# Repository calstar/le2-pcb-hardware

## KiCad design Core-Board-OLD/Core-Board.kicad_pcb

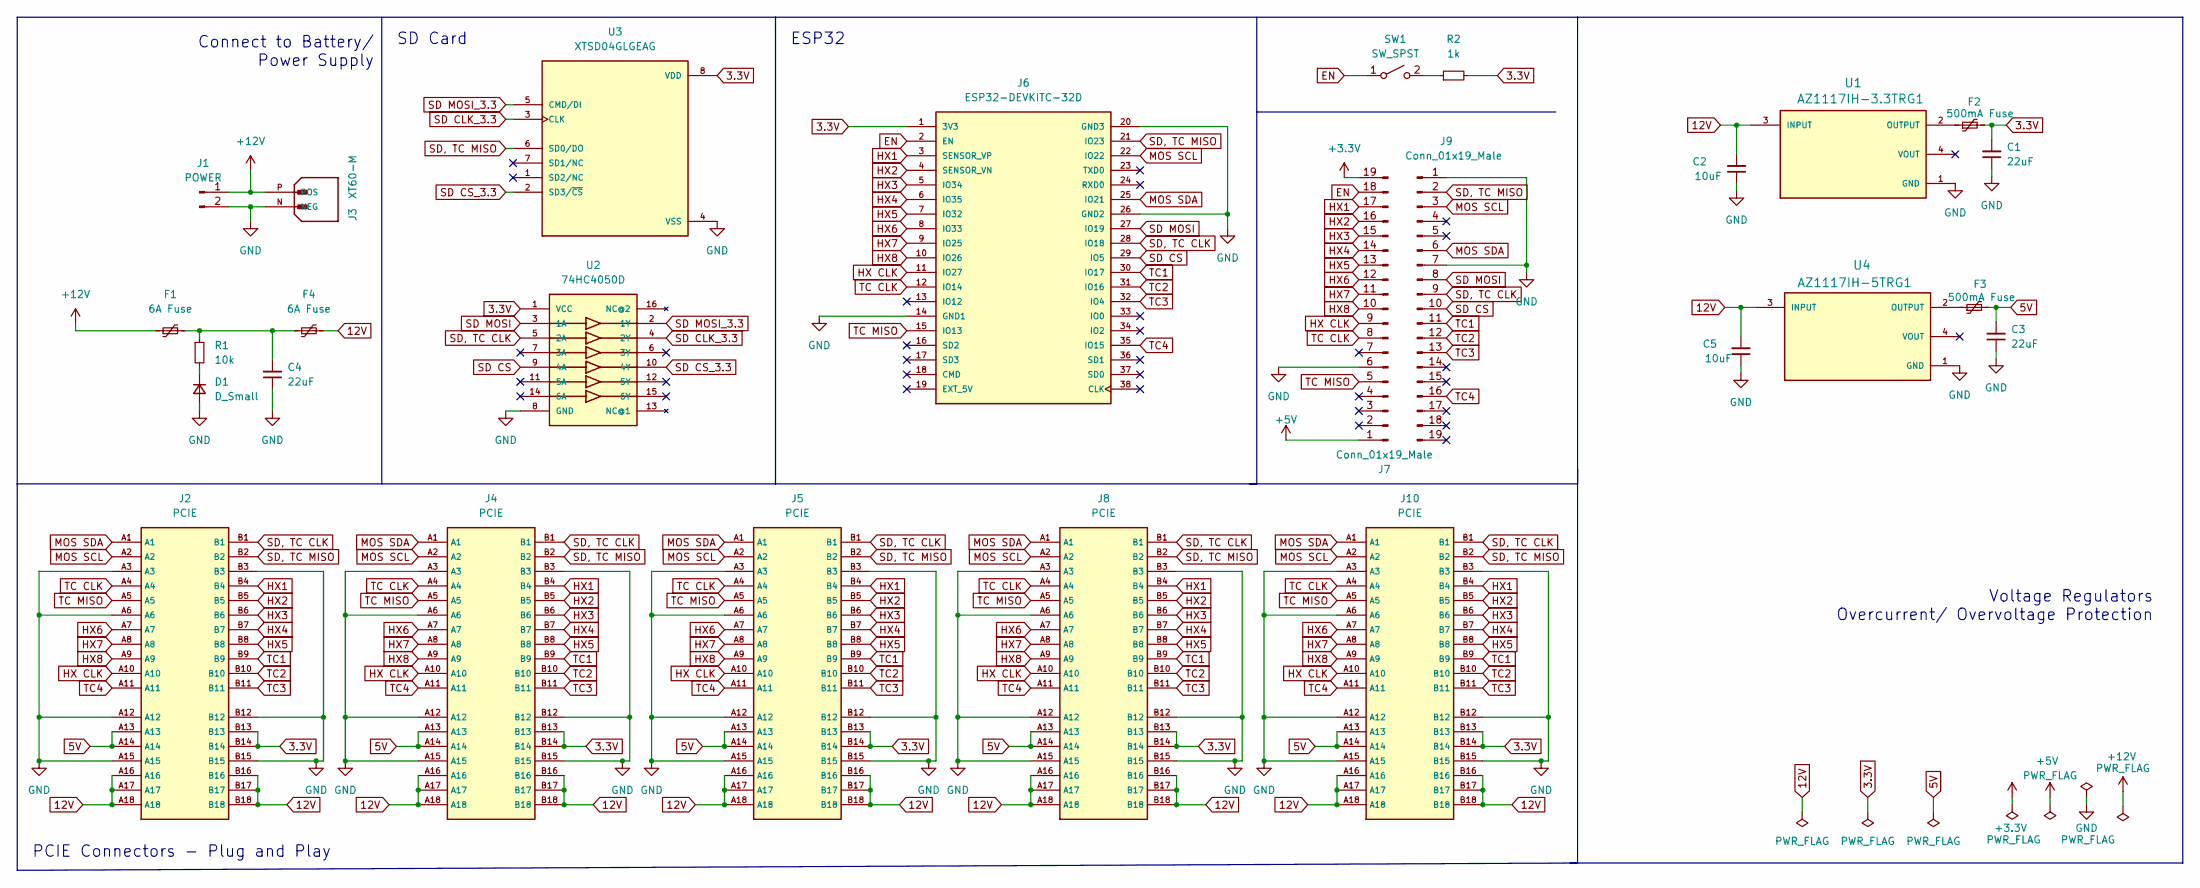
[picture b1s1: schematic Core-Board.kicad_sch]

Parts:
C1, C3, C4: 22uF; C_0603_1608Metric
C2, C5: 10uF; C_0603_1608Metric
D1: D_Small; D_0603_1608Metric
F1, F4: 6A Fuse; Fuse_2920_7451Metric
F2, F3: 500mA Fuse; Fuse_0603_1608Metric
J1: POWER; Banana_Jack_2Pin
J2, J4, J5, J8, J10: PCIE; AMPHENOL_10018784-10210TLF; PARTREV B
J3: XT60-M; AMASS_XT60-M; PARTREV V1.2
J6: ESP32-DEVKITC-32D; MODULE_ESP32-DEVKITC-32D; PARTREV 4
J7, J9: Conn_01x19_Male; PinHeader_1x19_P2.54mm_Vertical
R1: 10k; R_0603_1608Metric
R2: 1k; R_0603_1608Metric
SW1: SW_SPST; SW_PUSH_6mm
U1: AZ1117IH-3.3TRG1; SOT230P700X185-4N; PARTREV 2-2
U2: 74HC4050D; SO16
U3: XTSD04GLGEAG; SON127P600X800X95-8N; PARTREV 3.1
U4: AZ1117IH-5TRG1; SOT230P700X185-4N; PARTREV 2-2

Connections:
3.3V: C1.2, F2.2, J2.B13, J2.B14, J4.B13, J4.B14, J5.B13, J5.B14, J6.1 (3V3), J8.B13, J8.B14, J10.B13, J10.B14, R2.2, U2.1 (VCC), U3.8 (VDD)
5V: C3.2, F3.2, J2.A13, J2.A14, J4.A13, J4.A14, J5.A13, J5.A14, J8.A13, J8.A14, J10.A13, J10.A14
12V: C2.2, C5.2, F4.2, J2.A16, J2.A17, J2.A18, J2.B16, J2.B17, J2.B18, J4.A16, J4.A17, J4.A18, J4.B16, J4.B17, J4.B18, J5.A16, J5.A17, J5.A18, J5.B16, J5.B17, J5.B18, J8.A16, J8.A17, J8.A18, J8.B16, J8.B17, J8.B18, J10.A16, J10.A17, J10.A18, J10.B16, J10.B17, J10.B18, U1.3 (INPUT), U4.3 (INPUT)
+3.3V: J7.19
+5V: J7.1
+12V: F1.1, J1.1, J3.P (POS)
EN: J6.2 (EN), J7.18, SW1.1 (A)
GND: C1.1, C2.1, C3.1, C4.1, C5.1, D1.2 (A), J1.2, J2.A3, J2.A6, J2.A12, J2.A15, J2.B3, J2.B12, J2.B15, J3.N (NEG), J4.A3, J4.A6, J4.A12, J4.A15, J4.B3, J4.B12, J4.B15, J5.A3, J5.A6, J5.A12, J5.A15, J5.B3, J5.B12, J5.B15, J6.14 (GND1), J6.20 (GND3), J6.26 (GND2), J7.6, J8.A3, J8.A6, J8.A12, J8.A15, J8.B3, J8.B12, J8.B15, J9.1, J9.7, J10.A3, J10.A6, J10.A12, J10.A15, J10.B3, J10.B12, J10.B15, U1.1 (GND), U2.8 (GND), U3.4 (VSS), U4.1 (GND)
HX1: J2.B4, J4.B4, J5.B4, J6.3 (SENSOR_VP), J7.17, J8.B4, J10.B4
HX2: J2.B5, J4.B5, J5.B5, J6.4 (SENSOR_VN), J7.16, J8.B5, J10.B5
HX3: J2.B6, J4.B6, J5.B6, J6.5 (IO34), J7.15, J8.B6, J10.B6
HX4: J2.B7, J4.B7, J5.B7, J6.6 (IO35), J7.14, J8.B7, J10.B7
HX5: J2.B8, J4.B8, J5.B8, J6.7 (IO32), J7.13, J8.B8, J10.B8
HX6: J2.A7, J4.A7, J5.A7, J6.8 (IO33), J7.12, J8.A7, J10.A7
HX7: J2.A8, J4.A8, J5.A8, J6.9 (IO25), J7.11, J8.A8, J10.A8
HX8: J2.A9, J4.A9, J5.A9, J6.10 (IO26), J7.10, J8.A9, J10.A9
HX CLK: J2.A10, J4.A10, J5.A10, J6.11 (IO27), J7.9, J8.A10, J10.A10
MOS SCL: J2.A2, J4.A2, J5.A2, J6.22 (IO22), J8.A2, J9.3, J10.A2
MOS SDA: J2.A1, J4.A1, J5.A1, J6.25 (IO21), J8.A1, J9.6, J10.A1
unnamed: C4.2, F1.2, F4.1, R1.1
unnamed: D1.1 (K), R1.2
unnamed: F2.1, U1.2 (OUTPUT)
unnamed: F3.1, U4.2 (OUTPUT)
unnamed: R2.1, SW1.2 (B)
SD CLK_3.3: U2.4 (2Y), U3.3 (CLK)
SD CS: J6.29 (IO5), J9.10, U2.9 (4A)
SD CS_3.3: U2.10 (4Y), U3.2 (SD3/~CS)
SD MOSI: J6.27 (IO19), J9.8, U2.3 (1A)
SD MOSI_3.3: U2.2 (1Y), U3.5 (CMD/DI)
SD, TC CLK: J2.B1, J4.B1, J5.B1, J6.28 (IO18), J8.B1, J9.9, J10.B1, U2.5 (2A)
SD, TC MISO: J2.B2, J4.B2, J5.B2, J6.21 (IO23), J8.B2, J9.2, J10.B2, U3.6 (SD0/DO)
TC1: J2.B9, J4.B9, J5.B9, J6.30 (IO17), J8.B9, J9.11, J10.B9
TC2: J2.B10, J4.B10, J5.B10, J6.31 (IO16), J8.B10, J9.12, J10.B10
TC3: J2.B11, J4.B11, J5.B11, J6.32 (IO4), J8.B11, J9.13, J10.B11
TC4: J2.A11, J4.A11, J5.A11, J6.35 (IO15), J8.A11, J9.16, J10.A11
TC CLK: J2.A4, J4.A4, J5.A4, J6.12 (IO14), J7.8, J8.A4, J10.A4
TC MISO: J2.A5, J4.A5, J5.A5, J6.15 (IO13), J7.5, J8.A5, J10.A5

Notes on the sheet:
PCIE Connectors - Plug and Play
SD Card
ESP32
Voltage Regulators Overcurrent/ Overvoltage Protection
Connect to Battery/ Power Supply

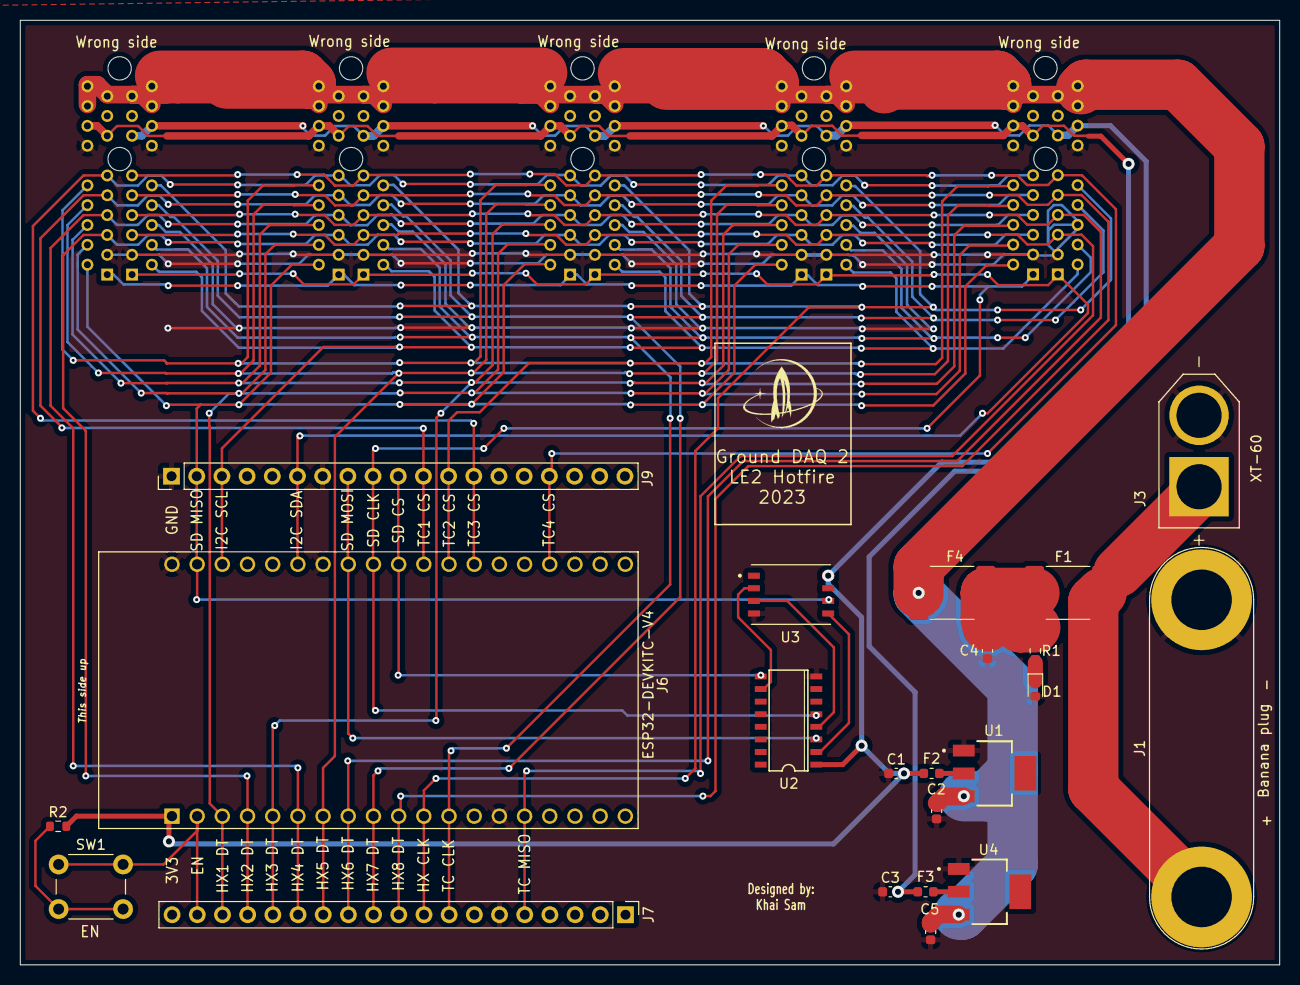
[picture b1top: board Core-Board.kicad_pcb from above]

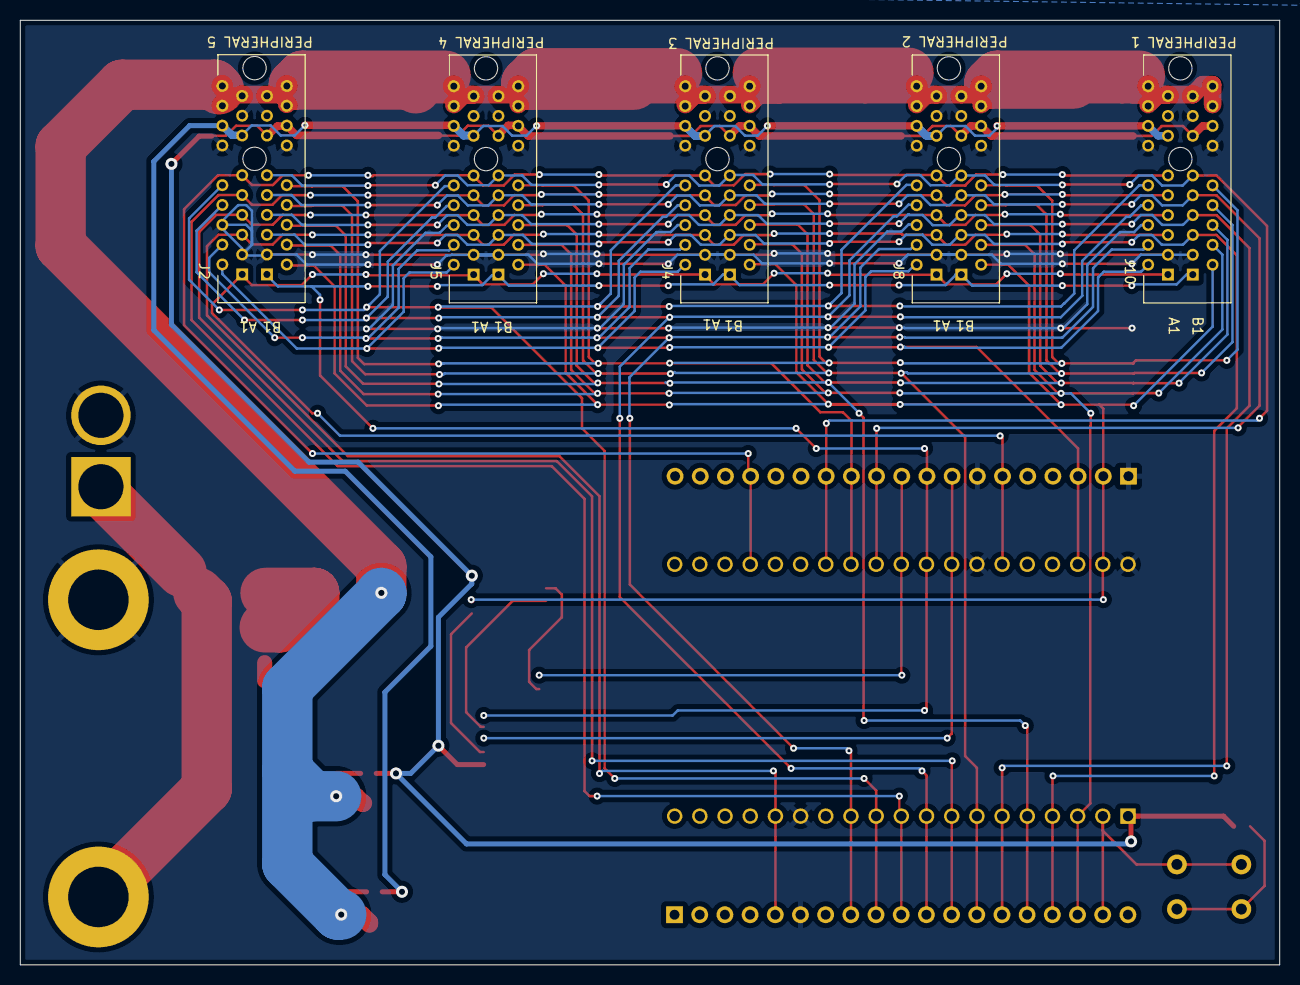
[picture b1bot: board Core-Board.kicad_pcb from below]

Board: 2 copper layers, 127.0 x 95.2 mm, 27 parts (5 on the bottom side), 35 nets.

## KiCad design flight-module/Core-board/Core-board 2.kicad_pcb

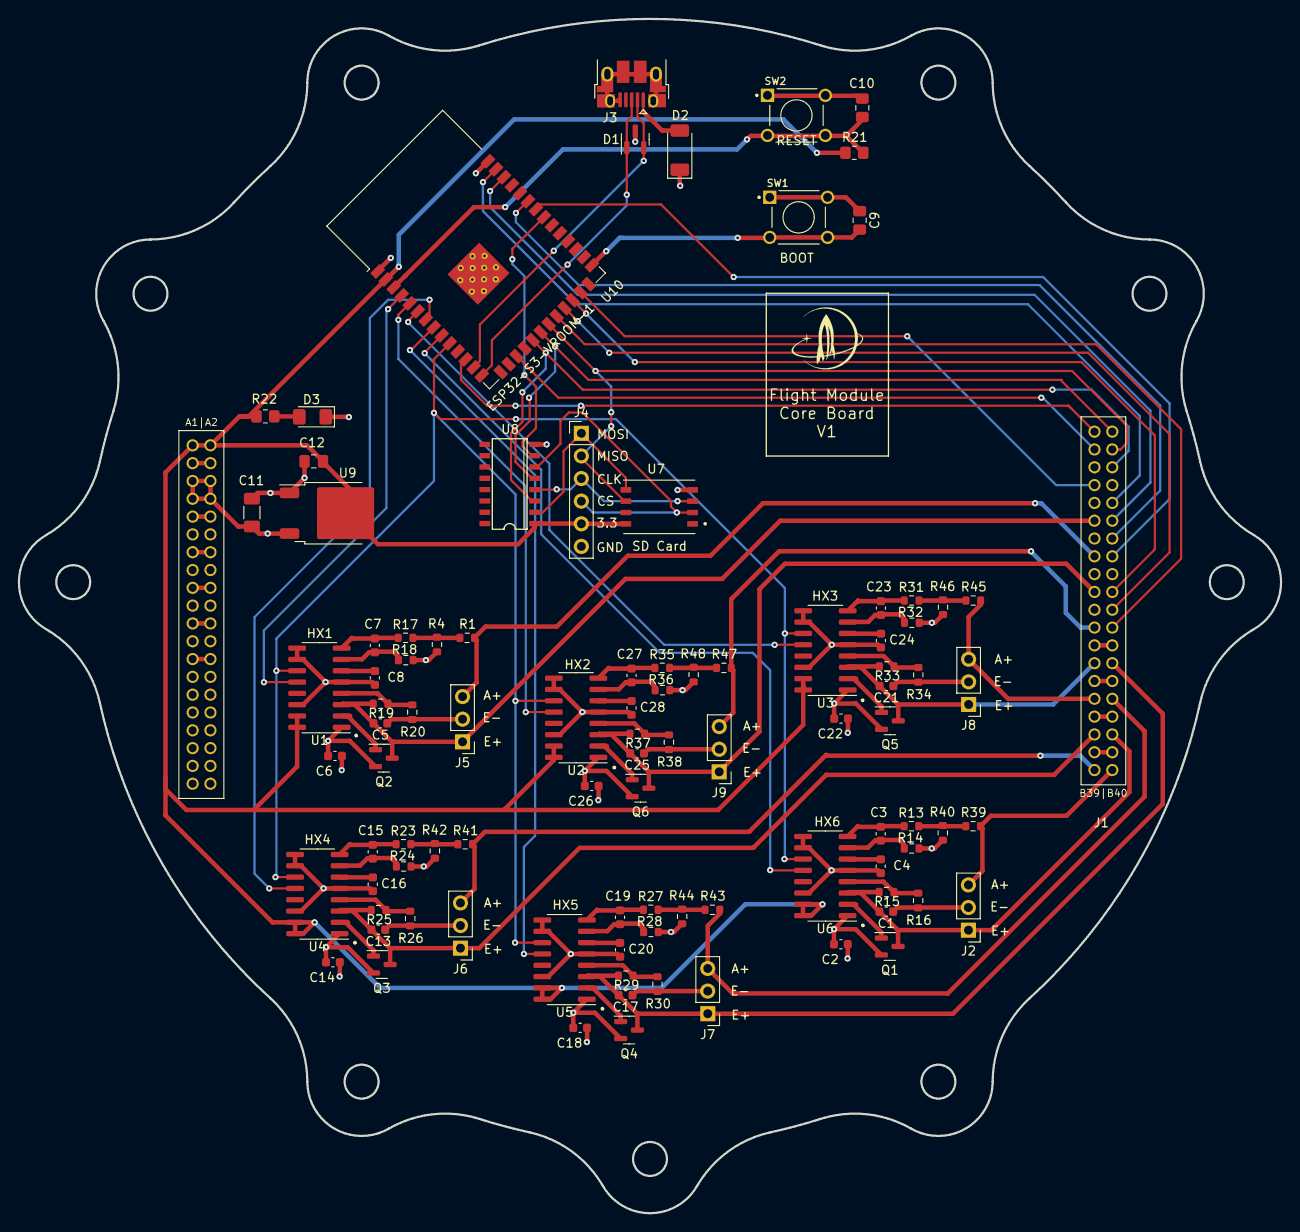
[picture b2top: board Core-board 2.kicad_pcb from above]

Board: 4 copper layers, 141.7 x 134.1 mm, 96 parts (0 on the bottom side), 81 nets.

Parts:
C1, C2, C5, C6, C13, C14, C17, C18, C21, C22, C25, C26: 10uF; C_0603_1608Metric
C3, C4, C7, C8, C15, C16, C19, C20, C23, C24, C27, C28: 0.1uF; C_0603_1608Metric
C9, C10: 1uF; C_0805_2012Metric_Pad1.18x1.45mm_HandSolder
C11: 10uF; C_1206_3216Metric_Pad1.33x1.80mm_HandSolder
C12: 22uF; C_0805_2012Metric_Pad1.18x1.45mm_HandSolder
D1: PESD12VL2BT; SOT-23
D2: D_Schottky; D_SOD-128
D3: GREEN; LED_1206_3216Metric_Pad1.42x1.75mm_HandSolder
J1: Stack_Shape
J2, J5, J6, J7, J8, J9: Conn_01x03_Pin; PinHeader_1x03_P2.54mm_Vertical
J3: USB_B_Micro; USB_Micro-B_Amphenol_10103594-0001LF_Horizontal
J4: Conn_01x06_Pin; PinHeader_1x06_P2.54mm_Vertical
Q1, Q2, Q3, Q4, Q5, Q6: MMBT4403LT3G; SOT-23
R1, R39, R41, R43, R45, R47: 100kΩ; R_0603_1608Metric
R4, R40, R42, R44, R46, R48: 2kΩ; R_0603_1608Metric
R13, R14, R17, R18, R23, R24, R27, R28, R31, R32, R35, R36: 100Ω; R_0603_1608Metric
R15, R19, R25, R29, R33, R37: 20kΩ; R_0603_1608Metric
R16, R20, R26, R30, R34, R38: 8.2kΩ; R_0603_1608Metric
R21: 10k; R_0805_2012Metric_Pad1.20x1.40mm_HandSolder
R22: 300; R_0805_2012Metric_Pad1.20x1.40mm_HandSolder
SW1, SW2: 1825910-6; SW_1825910-6-4
U1, U2, U3, U4, U5, U6: HX711; SOP-16_3.9x9.9mm_P1.27mm
U7: XTSD04GLGEAG; SON127P600X800X95-8N
U8: 74HC4050D; SO16
U9: AZ1084-3.3; TO-252-2
U10: ESP32-S3-WROOM-1-N16R2; ESP32-S3-WROOM-1

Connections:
+3.3V: C12.1, J1.A1 (Pin_1), J1.A2 (Pin_2), J4.5, R21.1, R22.2, U1.15 (RATE), U1.16 (DVDD), U2.15 (RATE), U2.16 (DVDD), U3.15 (RATE), U3.16 (DVDD), U4.15 (RATE), U4.16 (DVDD), U5.15 (RATE), U5.16 (DVDD), U6.15 (RATE), U6.16 (DVDD), U7.8 (VDD), U8.1 (VCC), U9.2 (VO), U10.2 (3V3)
+5V: C2.2, C6.2, C11.1, C14.2, C18.2, C22.2, C26.2, D2.1 (K), J1.A5 (Pin_5), J1.A6 (Pin_6), J1.A7 (Pin_7), J1.A8 (Pin_8), Q1.2 (E), Q2.2 (E), Q3.2 (E), Q4.2 (E), Q5.2 (E), Q6.2 (E), U1.1 (VSUP), U2.1 (VSUP), U3.1 (VSUP), U4.1 (VSUP), U5.1 (VSUP), U6.1 (VSUP), U9.3 (VI)
/ESP32-S3-WROOM-1-Breakout/BOOT: C9.1, SW1.3, SW1.4, U10.27 (IO0)
/ESP32-S3-WROOM-1-Breakout/EN: C10.1, R21.2, SW2.3, SW2.4, U10.3 (EN)
/ESP32-S3-WROOM-1-Breakout/USB_D+: D1.1 (K), J3.3 (D+), U10.14 (IO20)
/ESP32-S3-WROOM-1-Breakout/USB_D-: D1.2 (K), J3.2 (D-), U10.13 (IO19)
/HX1_A+: J1.B15 (Pin_15), J5.3, R1.1
/HX1_DT: U1.12 (DOUT), U10.4 (IO4)
/HX1_E+: C5.2, J1.B11 (Pin_11), J5.1, Q2.3 (C), R19.2, U1.3 (AVDD)
/HX2_A+: J1.B23 (Pin_23), J9.3, R47.1
/HX2_DT: U2.12 (DOUT), U10.5 (IO5)
/HX2_E+: C25.2, J1.B19 (Pin_19), J9.1, Q6.3 (C), R37.2, U2.3 (AVDD)
/HX3_A+: J1.B31 (Pin_31), J8.3, R45.1
/HX3_DT: U3.12 (DOUT), U10.6 (IO6)
/HX3_E+: C21.2, J1.B27 (Pin_27), J8.1, Q5.3 (C), R33.2, U3.3 (AVDD)
/HX4_A+: J1.B39 (Pin_39), J6.3, R41.1
/HX4_DT: U4.12 (DOUT), U10.7 (IO7)
/HX4_E+: C13.2, J1.B35 (Pin_35), J6.1, Q3.3 (C), R25.2, U4.3 (AVDD)
/HX5_A+: J1.B32 (Pin_32), J7.3, R43.1
/HX5_DT: U5.12 (DOUT), U10.8 (IO15)
/HX5_E+: C17.2, J1.B28 (Pin_28), J7.1, Q4.3 (C), R29.2, U5.3 (AVDD)
/HX6_A+: J1.B40 (Pin_40), J2.3, R39.1
/HX6_DT: U6.12 (DOUT), U10.9 (IO16)
/HX6_E+: C1.2, J1.B36 (Pin_36), J2.1, Q1.3 (C), R15.2, U6.3 (AVDD)
/HX_CLK: U1.11 (PD_SCK), U2.11 (PD_SCK), U3.11 (PD_SCK), U4.11 (PD_SCK), U5.11 (PD_SCK), U6.11 (PD_SCK), U10.10 (IO17)
/I2C_SCL: J1.B3 (Pin_3), U10.17 (IO9)
/I2C_SDA: J1.B1 (Pin_1), U10.12 (IO8)
/PYRO1EN: J1.B7 (Pin_7), U10.25 (IO48)
/PYRO2EN: J1.B20 (Pin_20), U10.24 (IO47)
/PYRO3EN: J1.B22 (Pin_22), U10.23 (IO21)
/PYRO4EN: J1.B24 (Pin_24), U10.22 (IO14)
/SD_CS: U8.7 (3A), U10.33 (IO40)
/SD_CS_BUF: J4.4, U7.2 (SD3/~CS), U8.6 (3Y)
/SPI_CLK: J1.B2 (Pin_2), U8.5 (2A), U10.20 (IO12)
/SPI_CLK_BUF: J4.3, U7.3 (CLK), U8.4 (2Y)
/SPI_MISO: J1.B4 (Pin_4), J4.2, U7.6 (SD0/DO), U10.21 (IO13)
/SPI_MOSI: J1.B6 (Pin_6), U8.3 (1A), U10.19 (IO11)
/SPI_MOSI_BUF: J4.1, U7.5 (CMD/DI), U8.2 (1Y)
/TC1_CS: J1.B10 (Pin_10), U10.39 (IO1)
/TC2_CS: J1.B12 (Pin_12), U10.38 (IO2)
/TC3_CS: J1.B14 (Pin_14), U10.35 (IO42)
/TC4_CS: J1.B16 (Pin_16), U10.34 (IO41)
GND: C1.1, C2.1, C4.1, C5.1, C6.1, C8.1, C9.2, C10.2, C11.2, C12.2, C13.1, C14.1, C16.1, C17.1, C18.1, C20.1, C21.1, C22.1, C24.1, C25.1, C26.1, C28.1, D1.3 (A), D3.1 (K), J1.A3 (Pin_3), J1.A4 (Pin_4), J1.A9 (Pin_9), J1.A10 (Pin_10), J1.A13 (Pin_13), J1.A14 (Pin_14), J1.A17 (Pin_17), J1.A18 (Pin_18), J1.A21 (Pin_21), J1.A22 (Pin_22), J1.A25 (Pin_25), J1.A26 (Pin_26), J1.B5 (Pin_5), J1.B8 (Pin_8), J1.B9 (Pin_9), J1.B13 (Pin_13), J1.B17 (Pin_17), J1.B18 (Pin_18), J1.B21 (Pin_21), J1.B25 (Pin_25), J1.B26 (Pin_26), J1.B29 (Pin_29), J1.B30 (Pin_30), J1.B33 (Pin_33), J1.B34 (Pin_34), J1.B37 (Pin_37), J1.B38 (Pin_38), J2.2, J3.5 (GND), J3.6 (Shield), J4.6, J5.2, J6.2, J7.2, J8.2, J9.2, R4.1, R14.2, R16.1, R18.2, R20.1, R24.2, R26.1, R28.2, R30.1, R32.2, R34.1, R36.2, R38.1, R40.1, R42.1, R44.1, R46.1, R48.1, SW1.1, SW1.2, SW2.1, SW2.2, U1.5 (AGND), U1.9 (INB-), U1.10 (INB+), U1.14 (XI), U2.5 (AGND), U2.9 (INB-), U2.10 (INB+), U2.14 (XI), U3.5 (AGND), U3.9 (INB-), U3.10 (INB+), U3.14 (XI), U4.5 (AGND), U4.9 (INB-), U4.10 (INB+), U4.14 (XI), U5.5 (AGND), U5.9 (INB-), U5.10 (INB+), U5.14 (XI), U6.5 (AGND), U6.9 (INB-), U6.10 (INB+), U6.14 (XI), U7.4 (VSS), U8.8 (GND), U9.1 (GND), U10.1 (GND), U10.40 (GND__1), U10.41 (GND__2)
unnamed: D2.2 (A), J3.1 (VBUS)
unnamed: D3.2 (A), R22.1
unnamed: Q1.1 (B), U6.2 (BASE)
unnamed: Q2.1 (B), U1.2 (BASE)
unnamed: Q3.1 (B), U4.2 (BASE)
unnamed: Q4.1 (B), U5.2 (BASE)
unnamed: Q5.1 (B), U3.2 (BASE)
unnamed: Q6.1 (B), U2.2 (BASE)
unnamed: R1.2, R4.2, R17.2
unnamed: R13.2, R39.2, R40.2
unnamed: R23.2, R41.2, R42.2
unnamed: R27.2, R43.2, R44.2
unnamed: R31.2, R45.2, R46.2
unnamed: R35.2, R47.2, R48.2
unnamed: C7.2, R17.1, U1.8 (INA+)
unnamed: C7.1, R18.1, U1.7 (INA-)
unnamed: C8.2, U1.6 (VBG)
unnamed: R19.1, R20.2, U1.4 (VFB)
unnamed: C27.2, R35.1, U2.8 (INA+)
unnamed: C27.1, R36.1, U2.7 (INA-)
unnamed: C28.2, U2.6 (VBG)
unnamed: R37.1, R38.2, U2.4 (VFB)
unnamed: C23.2, R31.1, U3.8 (INA+)
unnamed: C23.1, R32.1, U3.7 (INA-)
unnamed: C24.2, U3.6 (VBG)
unnamed: R33.1, R34.2, U3.4 (VFB)
unnamed: C15.2, R23.1, U4.8 (INA+)
unnamed: C15.1, R24.1, U4.7 (INA-)
unnamed: C16.2, U4.6 (VBG)
unnamed: R25.1, R26.2, U4.4 (VFB)
unnamed: C19.2, R27.1, U5.8 (INA+)
unnamed: C19.1, R28.1, U5.7 (INA-)
unnamed: C20.2, U5.6 (VBG)
unnamed: R29.1, R30.2, U5.4 (VFB)
unnamed: C3.2, R13.1, U6.8 (INA+)
unnamed: C3.1, R14.1, U6.7 (INA-)
unnamed: C4.2, U6.6 (VBG)
unnamed: R15.1, R16.2, U6.4 (VFB)

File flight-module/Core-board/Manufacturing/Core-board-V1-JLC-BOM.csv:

Comment,Designator,Footprint,LCSC
10uF,"C1,C2,C5,C6,C13,C14,C17,C18,C21,C22,C25,C26",Capacitor_SMD:C_0603_1608Metric,
10uF,C11,Capacitor_SMD:C_1206_3216Metric_Pad1.33x1.80mm_HandSolder,
22uF,C12,Capacitor_SMD:C_0805_2012Metric_Pad1.18x1.45mm_HandSolder,
0.1uF,"C3,C4,C7,C8,C15,C16,C19,C20,C23,C24,C27,C28",Capacitor_SMD:C_0603_1608Metric,
1uF,"C9,C10",Capacitor_SMD:C_0805_2012Metric_Pad1.18x1.45mm_HandSolder,
PESD12VL2BT,D1,Package_TO_SOT_SMD:SOT-23,
"PMEG3050EP,115",D2,Diode_SMD:D_SOD-128,
EL0603/GHC-C01/DT,D3,LED_SMD:LED_1206_3216Metric_Pad1.42x1.75mm_HandSolder,
MMBT4403LT3G,"Q1,Q2,Q3,Q4,Q5,Q6",Package_TO_SOT_SMD:SOT-23,
100Ω,"R13,R14,R17,R18,R23,R24,R27,R28,R31,R32,R35,R36",Resistor_SMD:R_0603_1608Metric,
20kΩ,"R15,R19,R25,R29,R33,R37",Resistor_SMD:R_0603_1608Metric,
8.2kΩ,"R16,R20,R26,R30,R34,R38",Resistor_SMD:R_0603_1608Metric,
10k,R21,Resistor_SMD:R_0805_2012Metric_Pad1.20x1.40mm_HandSolder,
300,R22,Resistor_SMD:R_0805_2012Metric_Pad1.20x1.40mm_HandSolder,
100kΩ,"R1,R39,R41,R43,R45,R47",Resistor_SMD:R_0603_1608Metric,
2kΩ,"R4,R40,R42,R44,R46,R48",Resistor_SMD:R_0603_1608Metric,
1825910-6,"SW1,SW2",Button_Switch_SMD:SW_SPST_TL3305A,
ESP32-S3-WROOM-1-N16R2,U10,RF_Module:ESP32-S3-WROOM-1,
XTSD04GLGEAG,U7,XTSD04GLGEAG:SON127P600X800X95-8N,
74HC4050D,U8,74HC4050D:SO16,
AZ1084-3.3,U9,Package_TO_SOT_SMD:TO-252-2,

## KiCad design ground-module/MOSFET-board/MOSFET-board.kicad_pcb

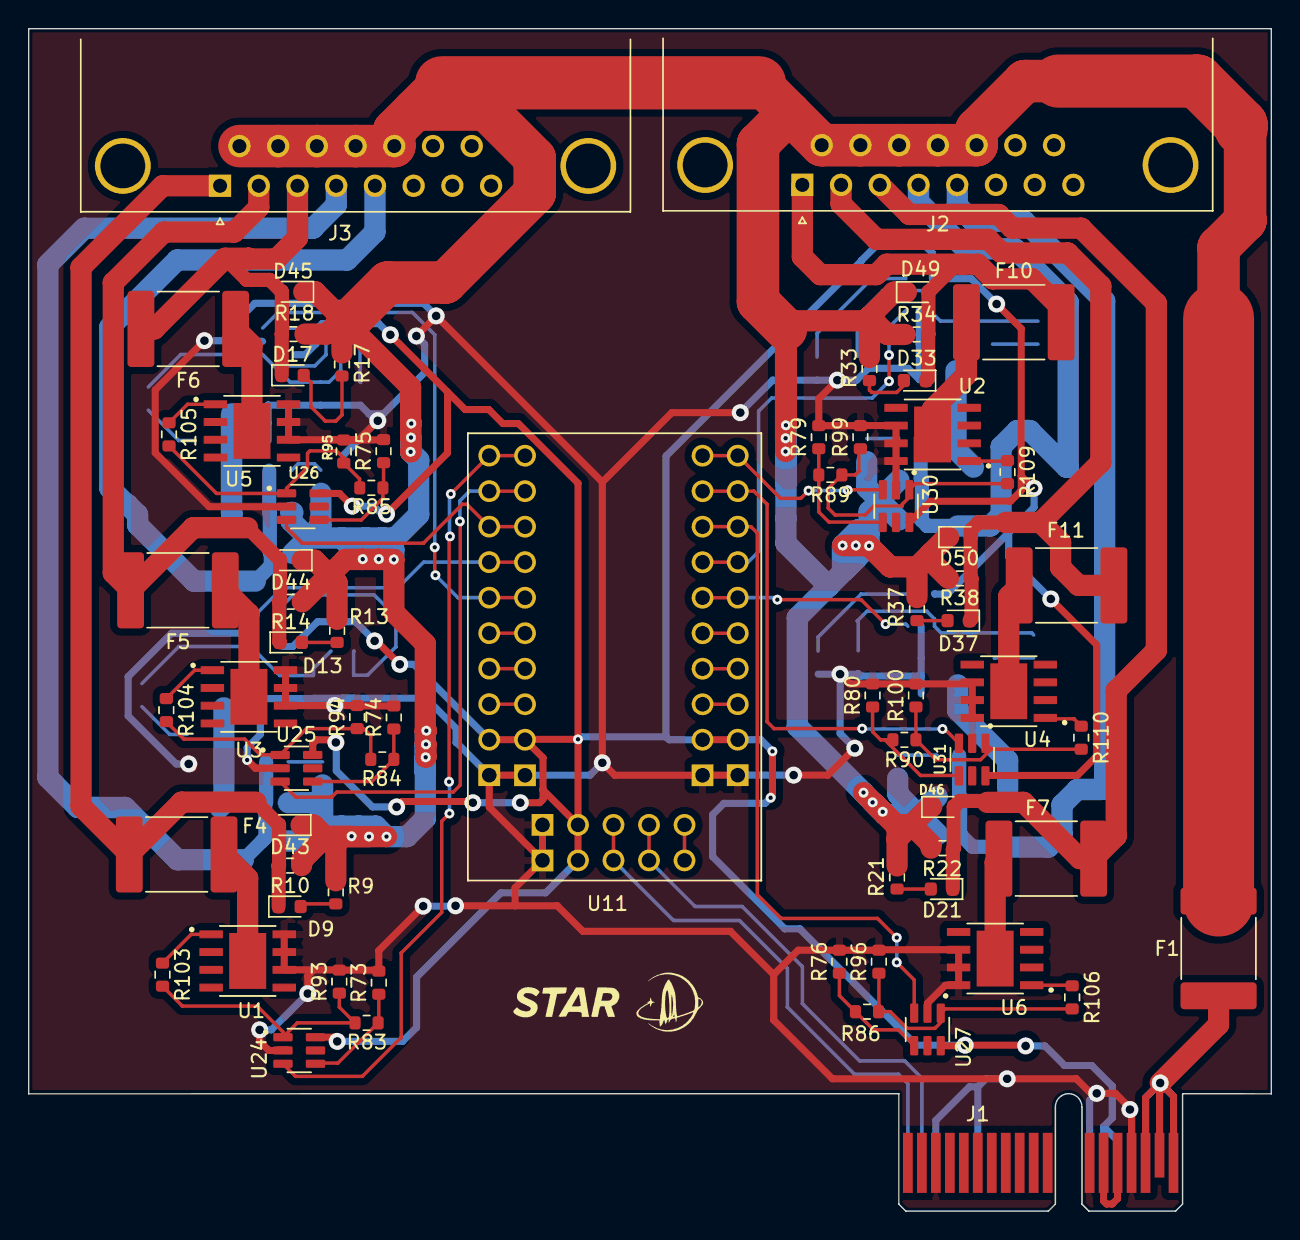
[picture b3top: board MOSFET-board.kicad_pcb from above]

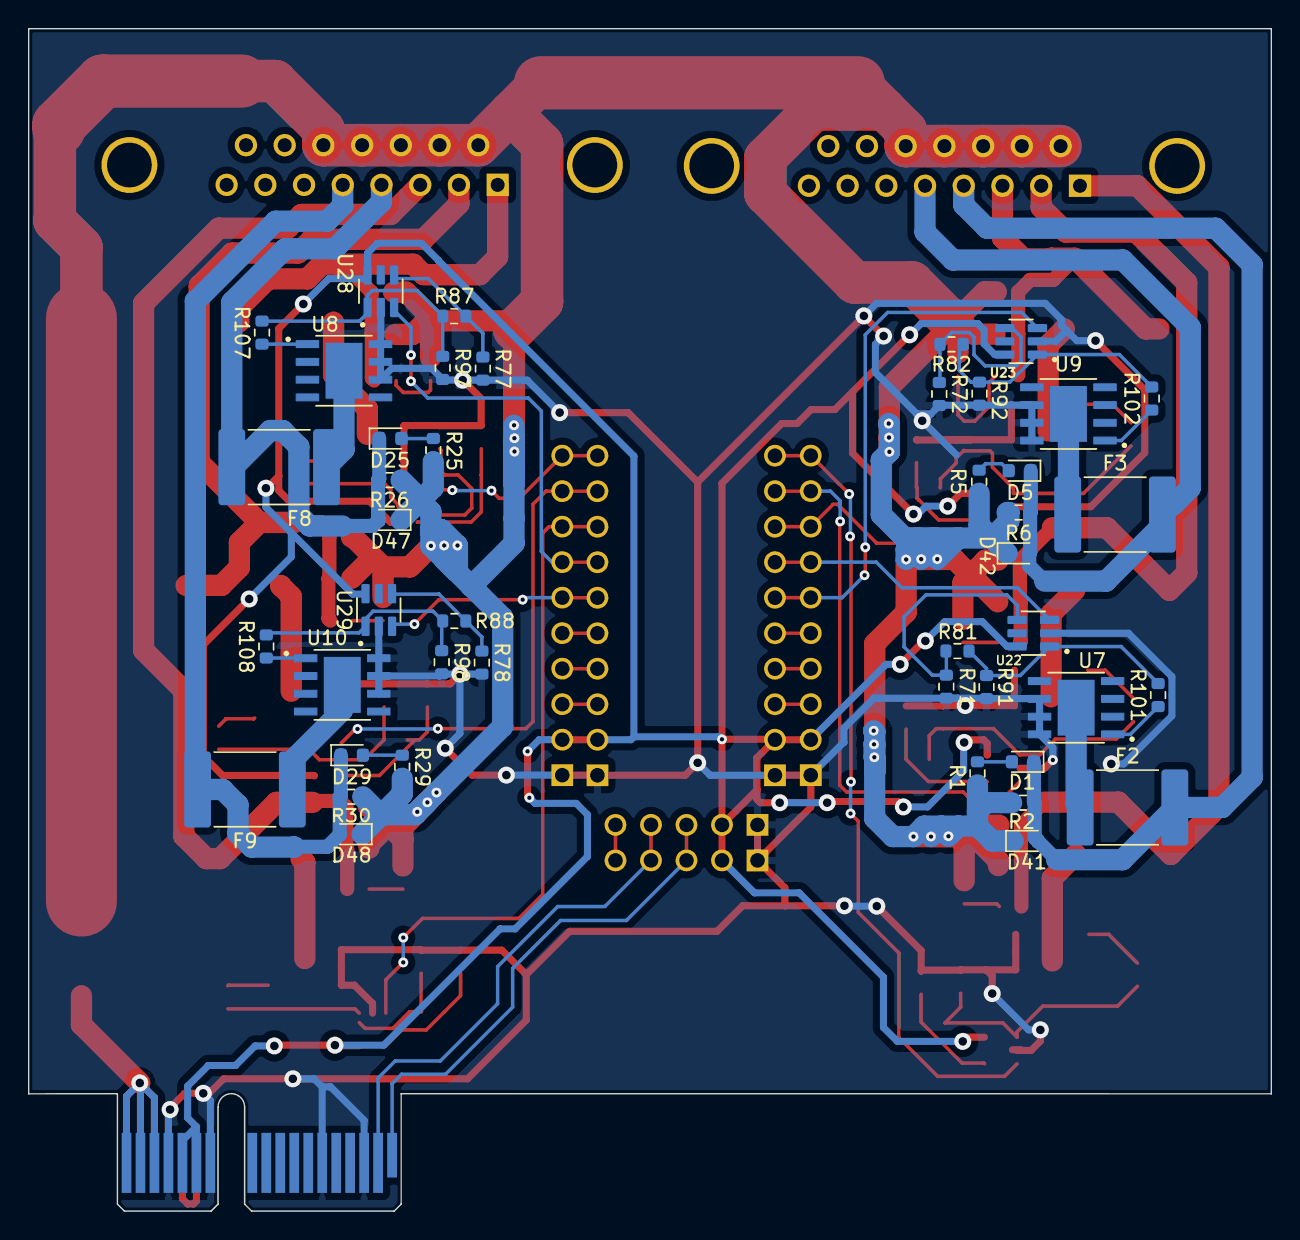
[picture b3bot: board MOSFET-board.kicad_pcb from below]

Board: 2 copper layers, 88.9 x 84.6 mm, 115 parts (44 on the bottom side), 77 nets.

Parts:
D1, D5, D9, D13, D17, D21, D25, D29, D33, D37: G_LED; LED_0603_1608Metric
D41, D42, D43, D44, D45, D46, D47, D48, D49, D50: D_Schottky; D_0603_1608Metric
F1: 6A Fuse; Fuse_2920_7451Metric
F2, F3, F4, F5, F6, F7, F8, F9, F10, F11: 3A Fuse; Fuse_2920_7451Metric
J1: PCIE-LP-01-01-F-DV-A-TR; BUS_PCIexpress_x1
J2, J3: DB15_Female; DSUB-15_Female_Horizontal_P2.77x2.84mm_EdgePinOffset7.70mm_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
R1, R5, R9, R13, R17, R21, R25, R29, R33, R37: 100; R_0603_1608Metric
R2, R6, R10, R14, R18, R22, R26, R30, R34, R38, R91, R92, R93, R94, R95, R96, R97, R98, R99, R100: 10k; R_0603_1608Metric
R71, R72, R73, R74, R75, R76, R77, R78, R79, R80: 1k; R_0603_1608Metric
R81, R82, R83, R84, R85, R86, R87, R88, R89, R90: 9k; R_0603_1608Metric
R101, R102, R103, R104, R105, R106, R107, R108, R109, R110: 2k; R_0603_1608Metric
U1, U2, U3, U4, U5, U6, U7, U8, U9, U10: BTS3080EJXUMA1; SOIC127P600X115-9N
U11: PCF8575_Breakout
U22, U23, U24, U25, U26, U27, U28, U29, U30, U31: ADA4897-1ARJZ-R7; SOT95P280X145-6N

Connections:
+3.3V: J1.B13, J1.B14
+5V: J1.A13, J1.A14, U11.9 (VDD), U11.12 (VCC), U11.17 (VDD), U22.6, U23.6, U24.6, U25.6, U26.6, U27.6, U28.6, U29.6, U30.6, U31.6
+12V: D41.1 (K), D42.1 (K), D43.1 (K), D44.1 (K), D45.1 (K), D46.1 (K), D47.1 (K), D48.1 (K), D49.1 (K), D50.1 (K), F1.2, J2.9, J2.10, J2.11 (P111), J2.12, J2.13, J3.9, J3.10, J3.11 (P111), J3.12, J3.13, R1.1, R2.1, R5.1, R6.1, R9.1, R10.1, R13.1, R14.1, R17.1, R18.1, R21.1, R22.1, R25.1, R26.1, R29.1, R30.1, R33.1, R34.1, R37.1, R38.1
GND: J1.A3, J1.A6, J1.A12, J1.A15, J1.B3, J1.B12, J1.B15, R71.2, R72.2, R73.2, R74.2, R75.2, R76.2, R77.2, R78.2, R79.2, R80.2, R91.2, R92.2, R93.2, R94.2, R95.2, R96.2, R97.2, R98.2, R99.2, R100.2, U1.6 (GND), U1.7 (GND), U1.8 (GND), U2.6 (GND), U2.7 (GND), U2.8 (GND), U3.6 (GND), U3.7 (GND), U3.8 (GND), U4.6 (GND), U4.7 (GND), U4.8 (GND), U5.6 (GND), U5.7 (GND), U5.8 (GND), U6.6 (GND), U6.7 (GND), U6.8 (GND), U7.6 (GND), U7.7 (GND), U7.8 (GND), U8.6 (GND), U8.7 (GND), U8.8 (GND), U9.6 (GND), U9.7 (GND), U9.8 (GND), U10.6 (GND), U10.7 (GND), U10.8 (GND), U11.10 (GND), U11.11 (GND), U11.16 (GND), U22.2, U23.2, U24.2, U25.2, U26.2, U27.2, U28.2, U29.2, U30.2, U31.2
I2C_SCL: J1.A2, U11.14 (SCL)
I2C_SDA: J1.A1, U11.13 (SDA)
unnamed: D1.2 (A), R1.2
unnamed: D5.2 (A), R5.2
unnamed: D9.2 (A), R9.2
unnamed: D13.2 (A), R13.2
unnamed: D17.2 (A), R17.2
unnamed: D21.2 (A), R21.2
unnamed: D25.2 (A), R25.2
unnamed: D29.2 (A), R29.2
unnamed: D33.2 (A), R33.2
unnamed: D37.2 (A), R37.2
unnamed: F1.1, J1.A16, J1.A17, J1.A18, J1.B16, J1.B17, J1.B18
unnamed: R71.1, R81.2, U22.4
unnamed: R72.1, R82.2, U23.4
unnamed: R73.1, R83.2, U24.4
unnamed: R74.1, R84.2, U25.4
unnamed: R75.1, R85.2, U26.4
unnamed: R76.1, R86.2, U27.4
unnamed: R77.1, R87.2, U28.4
unnamed: R78.1, R88.2, U29.4
unnamed: R79.1, R89.2, U30.4
unnamed: R80.1, R90.2, U31.4
unnamed: R90.1, R100.1, R110.2, U31.1
unnamed: R81.1, R91.1, R101.2, U22.1
unnamed: R82.1, R92.1, R102.2, U23.1
unnamed: R83.1, R93.1, R103.2, U24.1
unnamed: R84.1, R94.1, R104.2, U25.1
unnamed: R85.1, R95.1, R105.2, U26.1
unnamed: R86.1, R96.1, R106.2, U27.1
unnamed: R87.1, R97.1, R107.2, U28.1
unnamed: R88.1, R98.1, R108.2, U29.1
unnamed: R89.1, R99.1, R109.2, U30.1
unnamed: R103.1, U1.1 (IN)
unnamed: F4.1, U1.9 (OUT)
unnamed: R109.1, U2.1 (IN)
unnamed: F10.1, U2.9 (OUT)
unnamed: R104.1, U3.1 (IN)
unnamed: F5.1, U3.9 (OUT)
unnamed: R110.1, U4.1 (IN)
unnamed: F11.1, U4.9 (OUT)
unnamed: R105.1, U5.1 (IN)
unnamed: F6.1, U5.9 (OUT)
unnamed: R106.1, U6.1 (IN)
unnamed: F7.1, U6.9 (OUT)
unnamed: R101.1, U7.1 (IN)
unnamed: F2.1, U7.9 (OUT)
unnamed: R107.1, U8.1 (IN)
unnamed: F8.1, U8.9 (OUT)
unnamed: R102.1, U9.1 (IN)
unnamed: F3.1, U9.9 (OUT)
unnamed: R108.1, U10.1 (IN)
unnamed: F9.1, U10.9 (OUT)
PYRO1: D9.1 (K), D43.2 (A), F4.2, J3.1, R10.2
PYRO1EN: U11.1 (P10), U24.3
PYRO2: D33.1 (K), D49.2 (A), F10.2, J2.1, R34.2
PYRO2EN: U11.25 (P07), U30.3
PYRO3: D13.1 (K), D44.2 (A), F5.2, J3.2, R14.2
PYRO3EN: U11.2 (P11), U25.3
PYRO4: D37.1 (K), D50.2 (A), F11.2, J2.2, R38.2
PYRO4EN: U11.24 (P06), U31.3
PYRO5: D17.1 (K), D45.2 (A), F6.2, J3.3, R18.2
PYRO5EN: U11.3 (P12), U26.3
PYRO6: D21.1 (K), D46.2 (A), F7.2, J2.3, R22.2
PYRO6EN: U11.23 (P05), U27.3
PYRO7: D1.1 (K), D41.2 (A), F2.2, J3.4, R2.2
PYRO7EN: U11.4 (P13), U22.3
PYRO8: D25.1 (K), D47.2 (A), F8.2, J2.4, R26.2
PYRO8EN: U11.22 (P04), U28.3
PYRO9: D5.1 (K), D42.2 (A), F3.2, J3.5, R6.2
PYRO9EN: U11.5 (P14), U23.3
PYRO10: D29.1 (K), D48.2 (A), F9.2, J2.5, R30.2
PYRO10EN: U11.21 (P03), U29.3

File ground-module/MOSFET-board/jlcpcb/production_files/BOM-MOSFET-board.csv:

Comment,Designator,Footprint,LCSC
2k,"R101,R102,R103,R104,R105,R106,R107,R108,R109,R110",R_0603_1608Metric,C105576
D_Schottky,"D41,D42,D43,D44,D45,D46,D47,D48,D49,D50",D_0603_1608Metric,C143772
1k,"R71,R72,R73,R74,R75,R76,R77,R78,R79,R80",R_0603_1608Metric,C227458
9k,"R81,R82,R83,R84,R85,R86,R87,R88,R89,R90",R_0603_1608Metric,C3016444
10k,"R10,R100,R14,R18,R2,R22,R26,R30,R34,R38,R6,R91,R92,R93,R94,R95,R96,R97,R98,R99",R_0603_1608Metric,C327830
ADA4897-1ARJZ-R7,"U22,U23,U24,U25,U26,U27,U28,U29,U30,U31",SOT95P280X145-6N,C694752
100,"R1,R13,R17,R21,R25,R29,R33,R37,R5,R9",R_0603_1608Metric,C881893
